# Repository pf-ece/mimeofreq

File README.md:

# Mimeofreq

Digital delay + phaser combination guitar pedal. Further additions pending.

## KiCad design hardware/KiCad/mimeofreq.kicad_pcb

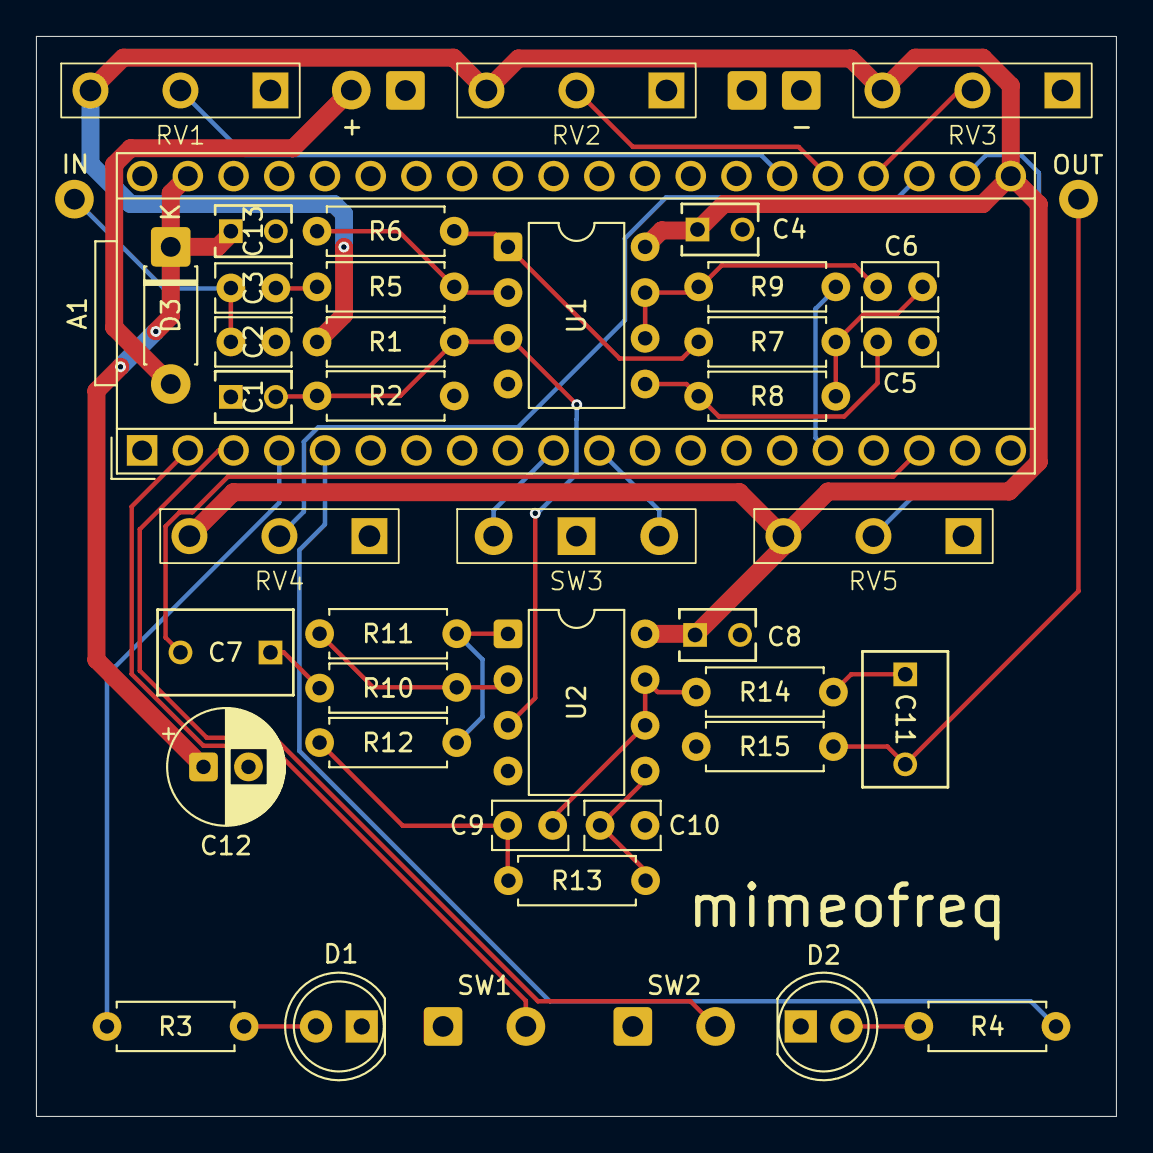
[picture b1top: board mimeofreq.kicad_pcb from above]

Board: 2 copper layers, 60.0 x 60.0 mm, 45 parts (0 on the bottom side), 35 nets.

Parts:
A1: Electrosmith_Daisy_Seed_Rev7; Electrosmith_Daisy_Seed
C1, C4, C8, C13: 100n; C_Rect_L4.0mm_W2.6mm_P2.50mm
C2: 100p; C_Rect_L4.0mm_W2.5mm_P2.50mm
C3: 10µ; C_Rect_L4.0mm_W2.5mm_P2.50mm
C5, C9: 1n; C_Rect_L4.0mm_W2.5mm_P2.50mm
C6, C10: 470p; C_Rect_L4.0mm_W2.5mm_P2.50mm
C7, C11: 1µ; C_Rect_L7.3mm_W4.5mm_P5.00mm
C12: 100μ; CP_Radial_D6.3mm_P2.50mm
D1, D2: LED; LED_D5.0mm
D3: 1N5817; D_DO-41_SOD81_P7.62mm_Horizontal
J1, J2: AudioJack2; SolderWire-0.5sqmm_1x02_P4.6mm_D0.9mm_OD2.1mm
J3: Jack-DC; SolderWire-0.5sqmm_1x02_P4.6mm_D0.9mm_OD2.1mm
R1, R2, R15: 100k; R_Axial_DIN0207_L6.3mm_D2.5mm_P7.62mm_Horizontal
R3, R4: 1k; R_Axial_DIN0207_L6.3mm_D2.5mm_P7.62mm_Horizontal
R5: 1M; R_Axial_DIN0207_L6.3mm_D2.5mm_P7.62mm_Horizontal
R6: 1M5; R_Axial_DIN0207_L6.3mm_D2.5mm_P7.62mm_Horizontal
R7, R8, R12, R13: 12k; R_Axial_DIN0207_L6.3mm_D2.5mm_P7.62mm_Horizontal
R9, R14: 100R; R_Axial_DIN0207_L6.3mm_D2.5mm_P7.62mm_Horizontal
R10: 33k; R_Axial_DIN0207_L6.3mm_D2.5mm_P7.62mm_Horizontal
R11: 22k; R_Axial_DIN0207_L6.3mm_D2.5mm_P7.62mm_Horizontal
RV1, RV2, RV3, RV4, RV5: 100k; Potentiometer_P160KN
SW1, SW2: SW_SPST; SolderWire-0.5sqmm_1x02_P4.6mm_D0.9mm_OD2.1mm
SW3: SW_SPDT; SolderWire-0.5sqmm_1x03_P4.6mm_D0.9mm_OD2.1mm_SPDT_OnOn
U1, U2: MCP6022; DIP-8_W7.62mm

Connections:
+3V3: A1.21 (3V3_A), C4.1, C8.1, R1.1, RV1.1, RV2.1, RV3.1, RV4.1, RV5.1, U1.8 (V+), U2.8 (V+)
+9V: D3.2 (A), J3.2
+9VCLEAN: A1.39 (VIN), C12.1, C13.1, D3.1 (K)
/FS1: A1.2 (SD_DATA_3), SW1.2 (B)
/FS2: A1.3 (SD_DATA_2), SW2.2 (B)
/IN: A1.16 (AUDIO_IN_1), R9.2
/Input Buffer/JACK_IN: C2.1, C3.2, J1.T
/LED1: A1.4 (SD_DATA_1), R3.1
/LED2: A1.5 (SD_DATA_0), R4.2
/OUT: A1.18 (AUDIO_OUT_1), C7.2
/Output Buffer/JACK_OUT: C11.2, J2.T, R15.1
/POT1: A1.26 (ADC_4), RV1.2
/POT2: A1.25 (ADC_3), RV2.2
/POT3: A1.24 (ADC_2), RV3.2
/POT4: A1.23 (ADC_1), RV4.2
/POT5: A1.22 (ADC_0), RV5.2
/SPDTa: A1.10 (SPI1_POCI), SW3.1 (A)
/SPDTb: A1.11 (SPI1_PICO), SW3.3 (C)
GND: A1.20 (AGND), A1.40 (DGND), C1.1, C2.2, C4.2, C6.2, C8.2, C10.2, C12.2, C13.2, D1.1 (K), D2.1 (K), J1.S, J2.S, J3.1, R2.2, R15.2, RV1.3, RV2.3, RV3.3, RV4.3, RV5.3, SW1.1 (A), SW2.1 (A), SW3.2 (B), U1.4 (V-), U2.4 (V-)
unnamed: C3.1, R5.1
unnamed: C5.1, R7.2, R8.1
unnamed: C7.1, R10.1
unnamed: C9.1, R12.2, R13.1
unnamed: C11.1, R14.2
unnamed: D1.2 (A), R3.2
unnamed: D2.2 (A), R4.1
unnamed: R6.2, R7.1, U1.1
unnamed: R11.2, R12.1, U2.1
unnamed: R5.2, R6.1, U1.2 (-)
unnamed: C6.1, R8.2, U1.5 (+)
unnamed: C5.2, R9.1, U1.6 (-), U1.7
unnamed: R10.2, R11.1, U2.2 (-)
unnamed: C10.1, R13.2, U2.5 (+)
unnamed: C9.2, R14.1, U2.6 (-), U2.7
VGND: C1.2, R1.2, R2.1, U1.3 (+), U2.3 (+)

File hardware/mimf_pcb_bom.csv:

"Reference","Qty","Value","DNP","Exclude from BOM","Exclude from Board","Footprint","Datasheet"
"A1","1","Electrosmith_Daisy_Seed_Rev7","","","","Module:Electrosmith_Daisy_Seed","https://static1.squarespace.com/static/58d03fdc1b10e3bf44256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"
"C1,C4,C8,C13","4","100n","","","","Capacitor_THT_Custom:C_Rect_L4.0mm_W2.6mm_P2.50mm",""
"C2","1","100p","","","","Capacitor_THT:C_Rect_L4.0mm_W2.5mm_P2.50mm",""
"C3","1","10u","","","","Capacitor_THT:C_Rect_L7.0mm_W2.5mm_P5.00mm",""
"C5,C9","2","1n","","","","Capacitor_THT:C_Rect_L4.0mm_W2.5mm_P2.50mm",""
"C6,C10","2","470p","","","","Capacitor_THT:C_Rect_L4.0mm_W2.5mm_P2.50mm",""
"C7,C11","2","1u","","","","Capacitor_THT_Custom:C_Rect_L7.3mm_W4.5mm_P5.00mm",""
"C12","1","100u","","","","Capacitor_THT:CP_Radial_D6.3mm_P2.50mm",""
"D1,D2","2","LED","","","","LED_THT:LED_D5.0mm",""
"D3","1","1N5817","","","","Diode_THT:D_DO-41_SOD81_P10.16mm_Horizontal","http://www.vishay.com/docs/88525/1n5817.pdf"
"J1,J2","2","AudioJack2","","","","Connector_Wire:SolderWire-0.5sqmm_1x02_P4.6mm_D0.9mm_OD2.1mm",""
"J3","1","Barrel_Jack_Switch_Pin3Ring","","","","Connector_Wire_Custom:SolderWire-0.5sqmm_1x03_P4.6mm_D0.9mm_OD2.1mm_BarrelJack",""
"R1,R2,R15","3","100k","","","","Resistor_THT:R_Axial_DIN0207_L6.3mm_D2.5mm_P7.62mm_Horizontal",""
"R3,R4","2","1k","","","","Resistor_THT:R_Axial_DIN0207_L6.3mm_D2.5mm_P7.62mm_Horizontal",""
"R5","1","1M","","","","Resistor_THT:R_Axial_DIN0207_L6.3mm_D2.5mm_P7.62mm_Horizontal",""
"R6","1","1M5","","","","Resistor_THT:R_Axial_DIN0207_L6.3mm_D2.5mm_P7.62mm_Horizontal",""
"R7,R8,R12,R13","4","12k","","","","Resistor_THT:R_Axial_DIN0207_L6.3mm_D2.5mm_P7.62mm_Horizontal",""
"R9,R14","2","100R","","","","Resistor_THT:R_Axial_DIN0207_L6.3mm_D2.5mm_P7.62mm_Horizontal",""
"R10","1","33k","","","","Resistor_THT:R_Axial_DIN0207_L6.3mm_D2.5mm_P7.62mm_Horizontal",""
"R11","1","22k","","","","Resistor_THT:R_Axial_DIN0207_L6.3mm_D2.5mm_P7.62mm_Horizontal",""
"RV1,RV2,RV3,RV4,RV5","5","100k","","","","Potentiometer_THT_Custom:Potentiometer_P160KN",""
"SW1,SW2","2","SW_SPST","","","","Connector_Wire:SolderWire-0.5sqmm_1x02_P4.6mm_D0.9mm_OD2.1mm",""
"SW3","1","SW_SPDT","","","","Connector_Wire_Custom:SolderWire-0.5sqmm_1x03_P4.6mm_D0.9mm_OD2.1mm_SPDT_OnOn",""
"U1,U2","2","MCP6022","","","","Package_DIP:DIP-8_W7.62mm","http://ww1.microchip.com/downloads/en/devicedoc/20001685e.pdf"

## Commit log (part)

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2026-05-09 Initial README.md
    Initial description of Freq-Fiche project.
2026-05-09 Heading capitalization
2026-05-10 Digital delay components; includes mix, feedback and time knobs. Adapted from related project coded earlier by me, 'delay1'.
2026-05-13 Added delay bypass switch.
2026-05-13 Removed unnecessary build files, these are generated when you run the code via VS Code. Code and hardware folders also added for organization.
2026-05-13 Setup for reverse delay mode.
2026-05-14 Low-pass filter for smoothing the delay time parameter.
2026-05-14 Relocates delay line into SDRAM.
2026-05-14 Function and variable initializations.
2026-05-16 Implementation of reverse delay mode.
2026-05-16 'code' folder renamed to 'source'.
2026-05-16 Setup for hold mode.
2026-05-19 Initial implementation of hold mode with added bug reports.
2026-05-21 Initial drill layout.
2026-05-21 Pot diameter correction.
2026-06-05 Converted into mono; only uses I/O channel 1.
2026-06-06 Initial phaser patch.
2026-06-07 Removed faulty resonance knob; added loadbang values.
2026-06-07 Heavy-compilable implementation of scale~ object.
2026-06-07 Heavy-compilable implementation of allpass~ object.
2026-06-11 Initial implementation of phaser effect.
2026-06-11 Removed 3-mode rotary switch.
2026-06-12 Initial delay-into-phaser implementation.
2026-06-13 Initial phaser-into-delay implementation.
2026-06-16 SPDT on-on switch implementation for combo effect modes.
2026-06-22 Initial input buffer LTspice schematic.
2026-06-22 Added temporary component footprints.
2026-06-22 Updated pedal effects info.
2026-06-23 Initial output buffer schematic.
2026-06-23 Implementation of LM7805 voltage regulator.
2026-06-24 Redesigned output buffer: filtering after buffering.
2026-06-24 Included third-party LTspice sub/sym files.
